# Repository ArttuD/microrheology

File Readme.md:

<div id="top"></div>

<!-- PROJECT LOGO -->
<br />
<div align="center">

  <h3 align="center">Microrheology Analysis Pipeline</h3>

  <p align="center">
    Authors: Ossi Arasalo and Arttu Lehtonen
    <br />
    Pokki Lab
    <br />
  </p>
</div>

<!-- TABLE OF CONTENTS -->
<details>
  <summary>Table of Contents</summary>
  <ol>
    <li><a href="#intro">Intro</a> </li>
    <li><a href="#tracker">Tracker</a></li>
    <li><a href="#sync">Syncronizer</a></li>
    <li><a href="#radius">Radius Estimator</a></li>
    <li><a href="#fit">Fit and Visualize</a></li>
  </ol>
</details>

<!-- ABOUT THE PROJECT -->
## Intro

### Requirements

```
pip install -r requirements.txt
```

# Pipeline

Our analysis pipeline is meant to analyze micromanipulation videos obtained via the measurement system introduced in X .The pipeline works as follows:

1. Particles are first tracked with ```track.py``` <br> Track all the files in the directory before moving to the next step.
2. Videos and current outputs from the coils has to be syncronized with ```sync.py```
3. Particles radius is estimated from separate sweep videos (manually changed focus over z) with ```radius.py```
4. Observed displacement signals are transformed into mechanical properties, namely to $|G|$ and $\phi$ with ```plot.py```. It also visualizes the results.

## Data folder structure 

```
- 22061401020201_A
  |- vid.mp4
  |- sweep.mp4
  |- current_trial_.txt
- 22061401020202_A
  |- vid.mp4
  |- current_trial_.txt
- 21081001010201_A
- 21081001010202_A
```

<br> Data can be found from: https://osf.io/jsxqh/ <br>

Each folder contains the timelapse video of particle movements (```vid.mp4```) (for instance output from [https://www.baslerweb.com/en/products/other-basler-software/basler-video-recording-software/](https://www.baslerweb.com/en/products/other-basler-software/basler-video-recording-software/). ```sweep.m4``` is the static video over the z stack, which is used to estimate the radius. This file has to be only in the first repeat. ```current_trial_.txt``` is the current output file.

**The naming convention is strict and the codes won't work if these are not followed**

```22061401020201_A```: 
* 220614: Year,month,day (zero padded 03 instad of 3)
* 01: sample 1
* 02: holder 2
* 02: location 2
* 01: repeat 1
* _A: sample matrix type

# Run instructions

## Tracker

Transform video into xy trajectories of particles.

```sh
python track.py -p ".../exampleData/Agarose30um/22061401020201_A"
```

2. i. Left click and drag a box around magnetic particles (drag from top left to bottom right) and release the left buttom. <br> press "q" to close the window <br>
 ii. Left click and drag a box around "small" reference particles (drag from top left to bottom right) and release the left buttom. <br> press "q" to close the window <br> iii. Left click and drag a box around cells (drag from top left to bottom right) and release the left buttom. <br> press "q" to close the window

3. Wait until tracking is over

## Syncronizer

The imaging and current control were performed with different computers that were not communicating with each others. Therefore, we needed to create an extra step to match the timestamps of the video and current file. Also absolute current values in the file are downscaled.

```sh
python sync.py -p ".../exampleData/Agarose30um"
```

2. Code displays current and displacement curves which both have calibration peaks in the beginning and in the end. The code automatically suggests a shif value. If it matches: i) close the window "q", ii) if you want to manual adjust the shift rough the shift value from top slider and fine tune <br>
   i) By default, the code displayes the average displacement within the field of view. Pressing "average" button, you can switch the the displacement of one big particle. This is useful of the curve is noisy<br>
   ii) if the autosyncronization is very off, you can pull the displacement curve to zero by pressing "local" button.<br>
  *** Event occurs when you move the slider next time<br>

# Match indices

Mathcing indices is not compulsory but is needed if the spheres are not tracked in the same order over the repeats or there is different number of particles tracked over the repeats.

```sh
python match_indices.py -p ".../exampleData/Agarose30um/*" --radius 61
```
### arguments
* ```--radius```: maximum distance in micrometers for shift in repeats
* ```-v```: visualize matching

# Radius Estimator

Radius estimate of the particle as a squared depence on |$G^*$|. We added an extra step to accurately define the size of each sphere. The code processes the z-swipe of the first repeat of each measurement and saves the results to later repeats

1. Run Radius Estimator code 
  ```sh
  python radius.py -p ".../exampleData/Agarose30um"
  ```
2. Code reads and processes the file: 1) reads the whole z-stack, 2) reads a cropped period of the video inwhich the maximum area is observed
3. Radius estimates of the particles are displayed. You can fix the automatic estimates by moving the red bars in the first two rows of the images.
4. Additionally you can do manual radius estimation by clicking the images which you want evaluate manually. Text ```manual``` appears on top of the image. Remember to move the red bars to the best focus so that manual estimation is easier.
5. Exit the visualization by pressing ```q```. A crop of the particle is displayed if you chose to do manual estimation. Drag an circle around its contours by pressing left mouse button, and dragging it on the other side of the particle before releasing

### Optional arguments
* ```--no_init```: Choose boxes manually
* ```--no_visualize```: Do not visualize
* ```--no_copy```: Do not copy radius estimates to repeats
* ```--repeats```: Also estimate radius for repeats that are missing from repeat 1. This might be inaccurate because the magnetic particles may have moved during the repeats (so the position of the box is slighly wrong)

# Analyze and Plot the Results

This script uses the files produced by previous scripts to find |$G^*$| and $\phi$ values. 

1. Run code 
  ```sh
  python plot.py -p ".../exampleData/Agarose30um -s "particle size (30 or 100 )" -l "x label of the plots (day/concetration/current/sample/holder/location)" -pixel_size "(basler_wide, basler_zoom...)"
  ```
Note: **concetration** or **current** are used in the paper

2. When the files are processed, results of spefic measurements are saved into their own folders and a summary of results and displayed plots are saved into a "results" folder created in ``` "*/example_files folder" ``` 

Other flags include
* ```--manual```: manually drop failed measurements by clicking them in the plots
* ```--flip```: Camera might 180 rotated so sinusoids are going the wrong way

All metadata (calibration constants and pixel to um) can be found from ```configs/default.ini```. Command line arguments are generated 
based on this file.

Own configuration can be also used by adding as the first argument e.g ```python plot.py own_config.ini -p ....```.

# Meta 

Force constants are hardcoded based on the particle size. Calibration codes are avalaible from us from request.

<!-- CONTACT -->
## Contact

- Ossi Arasalo  - ossi.arasalo@aalto.fi
- Arttu Lehtonen  - arttu.lehtonen@aalto.fi

Paper Link: [https://github.com/your_username/repo_name](https://github.com/your_username/repo_name)

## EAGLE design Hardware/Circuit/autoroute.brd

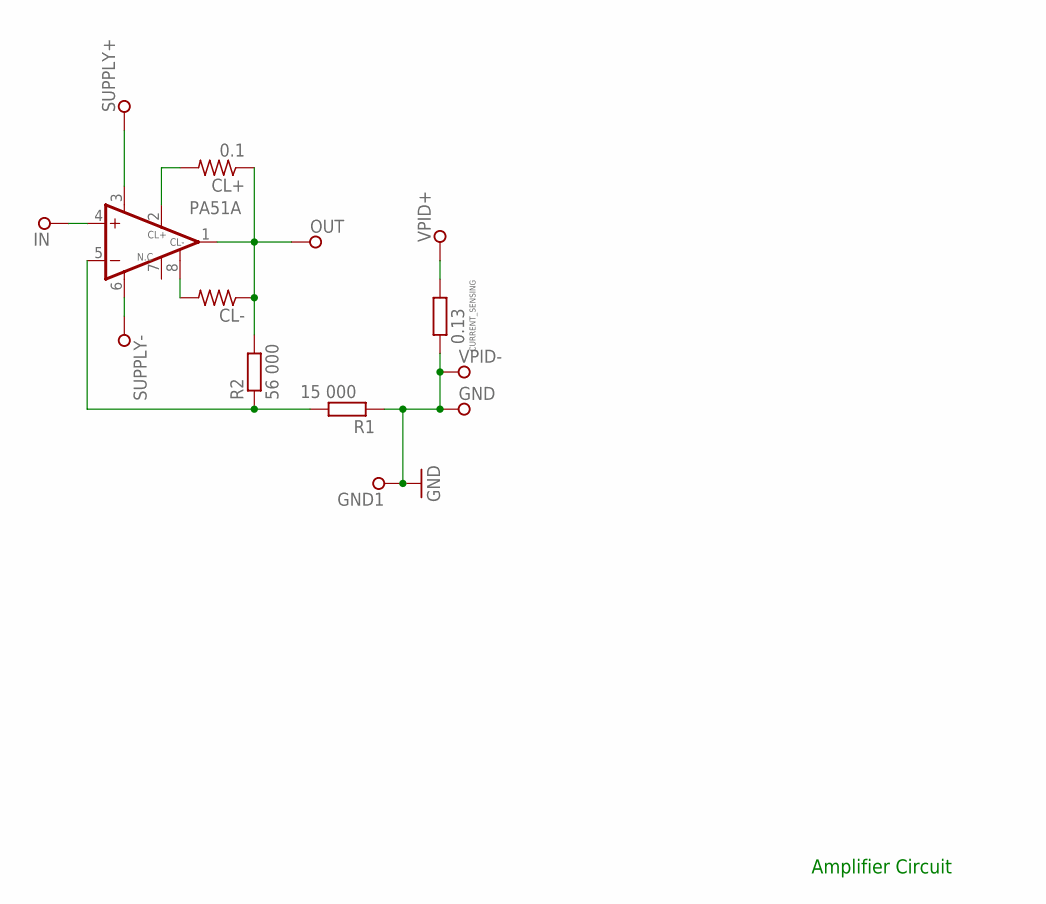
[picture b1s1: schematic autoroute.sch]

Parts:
CL+: 0.1; VTA56
CL-: R-US_VTA56; VTA56
CURRENT_SENSING: 0.13; V234/12
GND, GND1: SPECIAL_DRILL_0.2500; PAD_0.2500
IN: SPECIAL_DRILL_0.2500; PAD_0.2500
OUT: SPECIAL_DRILL_0.2500; PAD_0.2500
R1: 15 000; V234/12
R2: 56 000; V234/12
SUPPLY+: SPECIAL_DRILL_0.2500; PAD_0.2500
SUPPLY-: SPECIAL_DRILL_0.2500; PAD_0.2500
U$1: PA51A; 0804MC
VPID+: SPECIAL_DRILL_0.2500; PAD_0.2500
VPID-: SPECIAL_DRILL_0.2500; PAD_0.2500

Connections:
GND: CURRENT_SENSING.1, GND.1, GND1.1, R1.1, VPID-.1
unnamed: CL+.1, CL-.1, OUT.1, R2.2, U$1.1 (OUT)
unnamed: R1.2, R2.1, U$1.5 (-IN)
unnamed: CL-.2, U$1.8 (CL-)
unnamed: SUPPLY-.1, U$1.6 (V-)
unnamed: SUPPLY+.1, U$1.3 (V+)
unnamed: CL+.2, U$1.2 (CL+)
unnamed: CURRENT_SENSING.2, VPID+.1
unnamed: IN.1, U$1.4 (+IN)

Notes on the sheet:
Amplifier Circuit

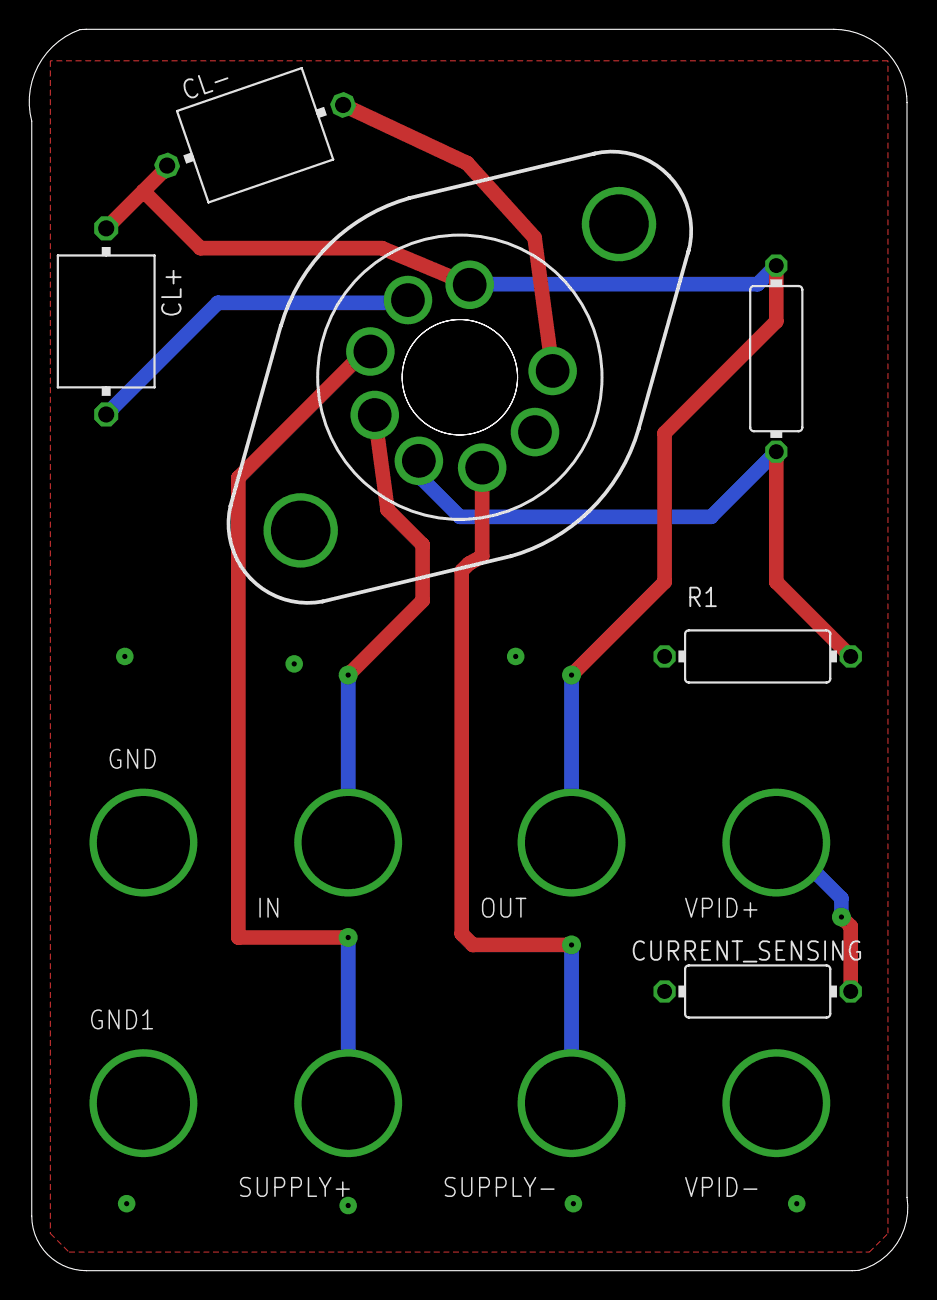
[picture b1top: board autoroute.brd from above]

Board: 2 copper layers, 59.9 x 84.7 mm, 14 parts (0 on the bottom side), 9 nets.

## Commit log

2022-08-02 init
2022-09-02 cleaning imports
2022-10-19 Added draft version of the amplifier ICs
2022-12-23 Vizualization
    Edited for an external users
2022-12-28 S8 figure fixes
    Agarose phase angle fixed from radian to degrees Fig S8 and Table 3.
2022-12-28 Data updated in https://osf.io/jsxqh/
2022-12-28 improved calibration and sample-to-sample variation
2022-12-28 Data repository path added
2022-12-28 path fixes
2022-12-29 removed old files
2023-01-05 change focus
2023-01-09 allow all repeats
2023-01-09 default false
2023-01-09 inverted flags
2023-01-09 Radius estimator information
2023-01-09 radius typo
2023-01-09 typos
2023-01-09 not visulize fixes
2023-01-09 interactively choose which beads to track manually
2023-01-09 edge case
2023-01-09 corner case
2023-01-09 _ problem fixed
2023-02-06 use track.json if track_matched not present
2023-02-13 check if videos are available
2023-02-13 added visualiztion. No manual. Handle single tracks properly
2023-02-13 match indices
2023-02-16 dont assume image size
2023-02-16 allow .avi files
2023-02-16 read mp4 and avi
2023-02-16 flippenderos
2023-02-17 Temporary Camera control code, QTpy6 viz soonish
2023-02-17 libs for camera
2023-02-20 Camera no stacks and pyQt draft
2023-02-21 default pixel size is now new camera. Arguments added
2023-02-24 flip sinusoid
2023-02-24 dtype
2023-02-24 1/pixel size
2023-02-24 the other way around
2023-02-27 increased buffer size
2023-02-27 reset to defaults after processing
2023-02-27 pixel size updated
2023-03-09 camera updates
2023-03-09 new camera code
2023-03-10 Working camera
2023-03-10 comments
2023-04-28 Arttu
2023-05-02 calibration model
2023-05-03 works with newer pandas
2023-05-11 updated pixel size
2023-05-23 Allow manually dropping failed measurements. Configurations in a file instead of hardcoded values.
2023-05-23 if manual override mask
2023-05-23 how to add own config files
2023-05-23 removed import
2023-05-23 pixel size
2023-05-23 config for hamamatsu
2023-05-23 wide hamamatsu
2023-05-23 naming
2023-05-23 config generation
2023-05-23 50 um fv
2023-05-23 f/v from avg to amp
2023-05-23 draw more plots
2023-05-23 logging
2023-05-26 1 sized plots
2023-06-19 osx bois
2023-09-18 allow flipped sinusoids
2023-10-06 Deleted not relevant
2023-10-06 New interface
2023-10-06 changed cv2 writer to ffmpeg
2023-12-11 flip has to be used. Fixed if all measurements fails
2023-12-11 break
2023-12-12 plot still if missing datapoints
2023-12-14 turn timelapse experiment into correct folder structure. Change sinusoid start time for fitting
2023-12-15 step int
2023-12-15 correct path for logging
2023-12-27 camera interface
2024-01-19 Camera
2024-01-23 fixed Qthreads for camera interface. prev pushes lazy comments. Sorry :)
2024-01-23 Threading for actual measurement
2024-01-24 zstack thread and cleaned the code
2024-12-18 Added turku argument
